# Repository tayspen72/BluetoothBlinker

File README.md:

Objective:
The goal of the project is to help myself become more familiar with the electronics design process. This includes:
* Schematic Design
* Component Selection
* PCB Layout
* Initial Board Bring-Up and Verification
* Firmware Development
* Evaluate Rust in an embedded microcontroller application

Plan
Build a PCB project with a similar purpose to a manufacturer evalutation kit with the following requirements:
* Bluetooth connectivity
* IO available with _reasonable_ function through peripherals
* Connectible to PC using USB-C
* Logging through UART when connected to PC

Conclusion:
The board design was completed and peer reviewed (by coworker)
Samples were ordered through PCB way and digikey for components
Samples were hand assembled (with blood sweat and tears)
Issue in the inline fuse, replaced with 0R resistor to advance in design
Board is functional, able to program and toggle LED using available IO
Bluetooth connectivity is pending..

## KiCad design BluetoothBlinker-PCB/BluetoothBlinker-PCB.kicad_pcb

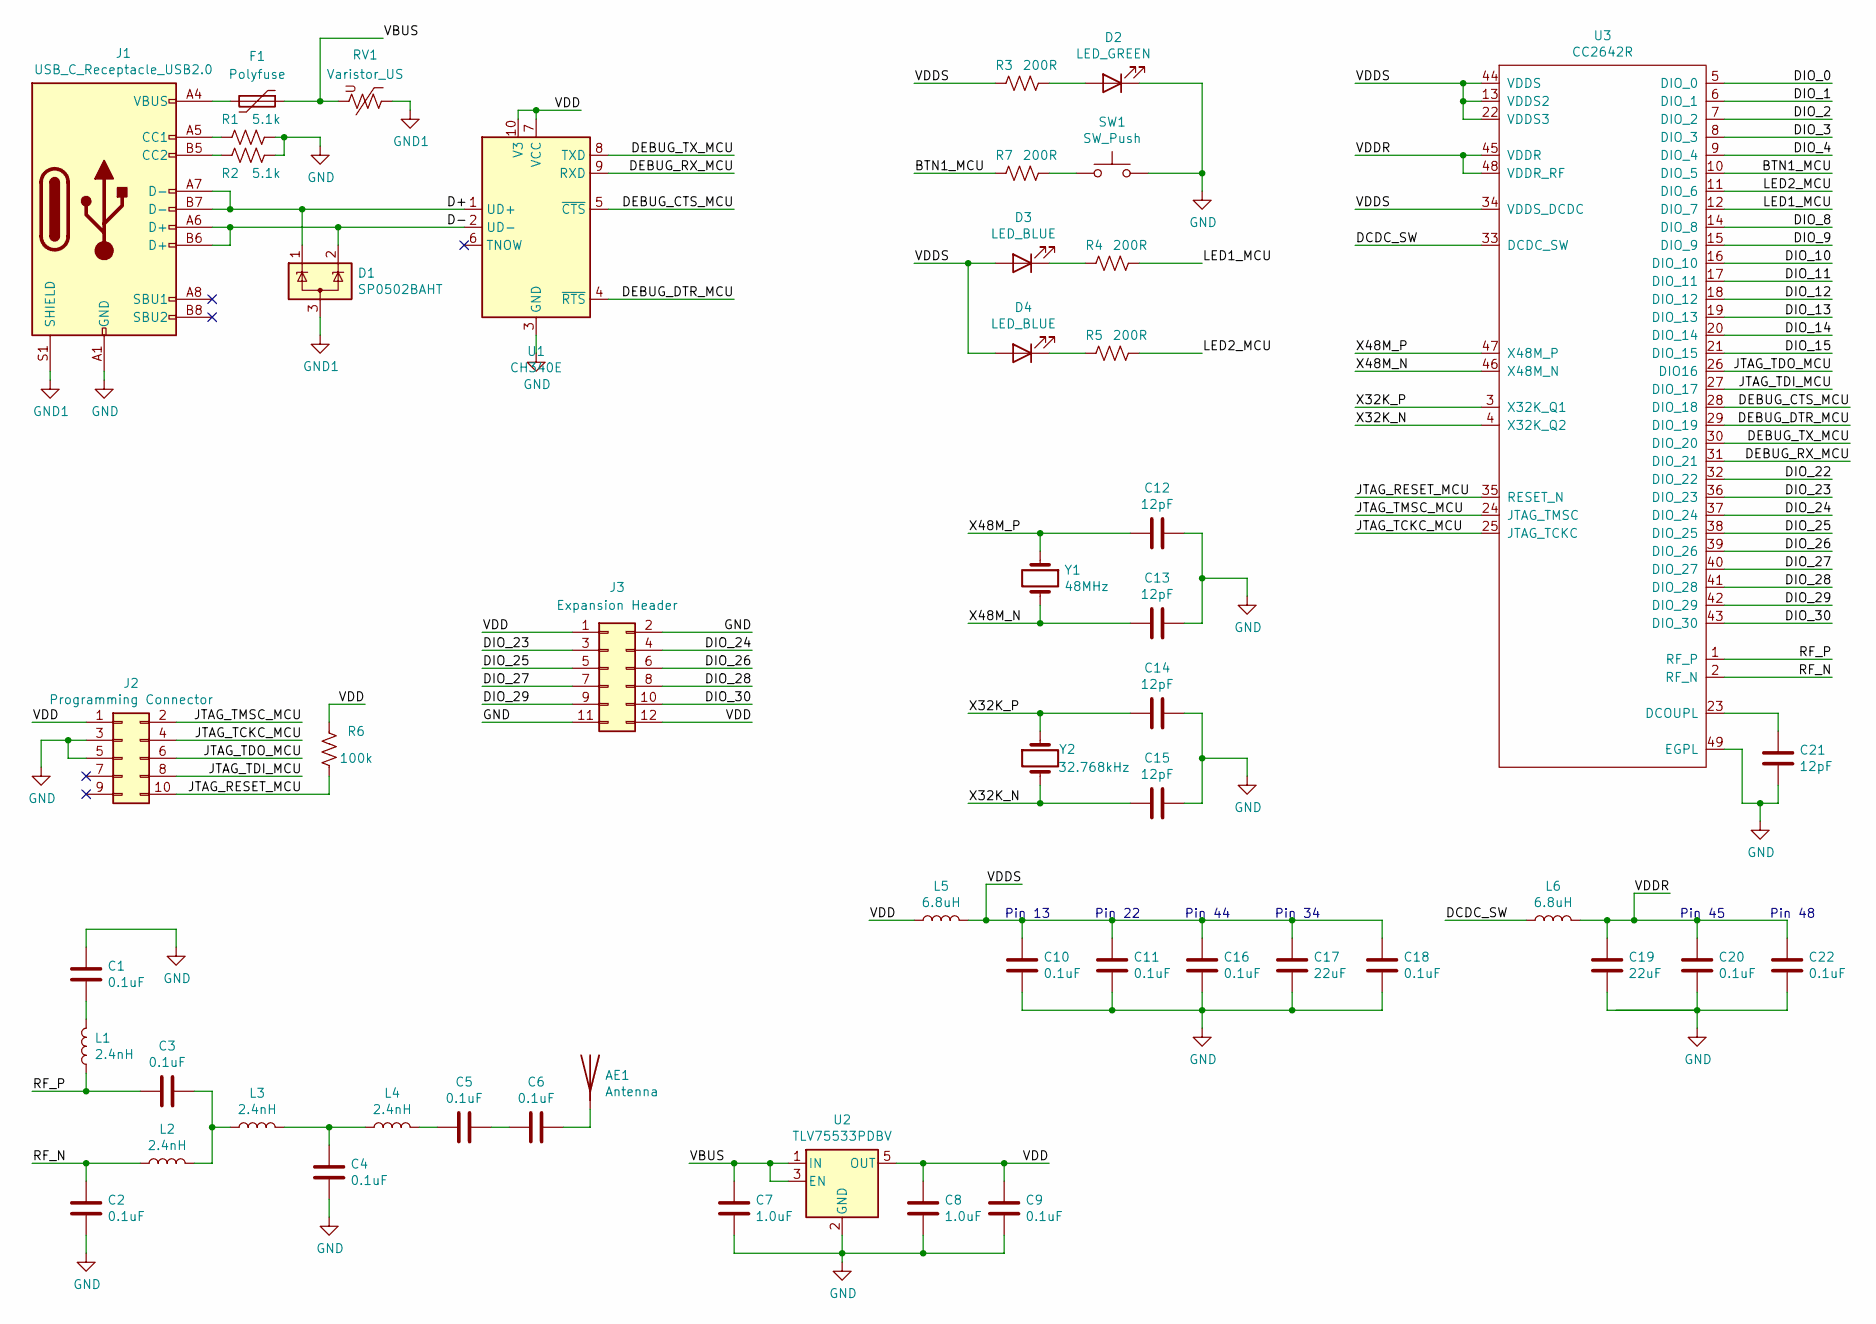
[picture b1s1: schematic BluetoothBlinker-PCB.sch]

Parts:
AE1: Antenna; Texas_SWRA117D_2.4GHz_Right
C1, C2, C3, C4, C5, C6, C9, C10, C11, C16, C18, C20, C22: 0.1uF; C_0603_1608Metric
C7, C8: 1.0uF; C_0603_1608Metric
C12, C13, C14, C15, C21: 12pF; C_0603_1608Metric
C17, C19: 22uF; C_0603_1608Metric
D1: SP0502BAHT; SOT-23
D2: LED_GREEN; LED_0603_1608Metric
D3, D4: LED_BLUE; LED_0603_1608Metric
F1: Polyfuse; R_1206_3216Metric
J1: USB_C_Receptacle_USB2.0; USB_C_Receptacle_GCT_USB4085
J2: Programming Connector; PinHeader_2x05_P1.27mm_Vertical
J3: Expansion Header; PinHeader_2x06_P2.54mm_Vertical
L1, L2, L3, L4: 2.4nH; L_0603_1608Metric
L5, L6: 6.8uH; L_0603_1608Metric
R1, R2: 5.1k; R_0603_1608Metric
R3, R4, R5, R7: 200R; R_0603_1608Metric
R6: 100k; R_0603_1608Metric
RV1: Varistor_US; R_0603_1608Metric
SW1: SW_Push; SW_PUSH_6mm
U1: CH340E; MSOP-10_3x3mm_P0.5mm
U2: TLV75533PDBV; SOT-23-5
U3: CC2642R
Y1: 48MHz; Crystal_HC49-U_Vertical
Y2: 32.768kHz; Crystal_C26-LF_D2.1mm_L6.5mm_Horizontal

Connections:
/BTN1_MCU: R7.1, U3.10 (DIO_5)
/D+: D1.1 (K), J1.A7 (D-), J1.B7 (D-), U1.1 (UD+)
/D-: D1.2 (K), J1.A6 (D+), J1.B6 (D+), U1.2 (UD-)
/DCDC_SW: L6.1, U3.33 (DCDC_SW)
/DEBUG_CTS_MCU: U1.5 (~CTS), U3.28 (DIO_18)
/DEBUG_DTR_MCU: U1.4 (~RTS), U3.29 (DIO_19)
/DEBUG_RX_MCU: U1.9 (RXD), U3.31 (DIO_21)
/DEBUG_TX_MCU: U1.8 (TXD), U3.30 (DIO_20)
/DIO_0: U3.5 (DIO_0)
/DIO_1: U3.6 (DIO_1)
/DIO_2: U3.7 (DIO_2)
/DIO_3: U3.8 (DIO_3)
/DIO_4: U3.9 (DIO_4)
/DIO_8: U3.14 (DIO_8)
/DIO_9: U3.15 (DIO_9)
/DIO_10: U3.16 (DIO_10)
/DIO_11: U3.17 (DIO_11)
/DIO_12: U3.18 (DIO_12)
/DIO_13: U3.19 (DIO_13)
/DIO_14: U3.20 (DIO_14)
/DIO_15: U3.21 (DIO_15)
/DIO_22: U3.32 (DIO_22)
/DIO_23: J3.3, U3.36 (DIO_23)
/DIO_24: J3.4, U3.37 (DIO_24)
/DIO_25: J3.5, U3.38 (DIO_25)
/DIO_26: J3.6, U3.39 (DIO_26)
/DIO_27: J3.7, U3.40 (DIO_27)
/DIO_28: J3.8, U3.41 (DIO_28)
/DIO_29: J3.9, U3.42 (DIO_29)
/DIO_30: J3.10, U3.43 (DIO_30)
/JTAG_RESET_MCU: J2.10, R6.1, U3.35 (RESET_N)
/JTAG_TCKC_MCU: J2.4, U3.25 (JTAG_TCKC)
/JTAG_TDI_MCU: J2.8, U3.27 (DIO_17)
/JTAG_TDO_MCU: J2.6, U3.26 (DIO16)
/JTAG_TMSC_MCU: J2.2, U3.24 (JTAG_TMSC)
/LED1_MCU: R4.2, U3.12 (DIO_7)
/LED2_MCU: R5.2, U3.11 (DIO_6)
/RF_N: C2.1, L2.1, U3.2 (RF_N)
/RF_P: C3.2, L1.1, U3.1 (RF_P)
/VBUS: C7.1, F1.1, RV1.2, U2.1 (IN), U2.3 (EN)
/VDD: C8.1, C9.1, J2.1, J3.1, J3.12, L5.1, R6.2, U1.7 (VCC), U1.10 (V3), U2.5 (OUT)
/VDDR: C19.1, C20.1, C22.1, L6.2, U3.45 (VDDR), U3.48 (VDDR_RF)
/VDDS: C10.1, C11.1, C16.1, C17.1, C18.1, D3.2 (A), D4.2 (A), L5.2, R3.1, U3.13 (VDDS2), U3.22 (VDDS3), U3.34 (VDDS_DCDC), U3.44 (VDDS)
/X32K_N: C15.2, U3.4 (X32K_Q2), Y2.2
/X32K_P: C14.2, U3.3 (X32K_Q1), Y2.1
/X48M_N: C13.2, U3.46 (X48M_N), Y1.2
/X48M_P: C12.2, U3.47 (X48M_P), Y1.1
GND: C1.2, C2.2, C4.2, C7.2, C8.2, C9.2, C10.2, C11.2, C12.1, C13.1, C14.1, C15.1, C16.2, C17.2, C18.2, C19.2, C20.2, C21.1, C22.2, D2.1 (K), J1.A1 (GND), J1.A12 (GND), J1.B1 (GND), J1.B12 (GND), J2.3, J2.5, J3.2, J3.11, R1.1, R2.1, SW1.2, U1.3 (GND), U2.2 (GND), U3.49 (EGPL)
GND1: D1.3 (A), J1.S1 (SHIELD), RV1.1
unnamed: AE1.1, C6.1
unnamed: C1.1, L1.2
unnamed: C3.1, L2.2, L3.1
unnamed: C4.1, L3.2, L4.1
unnamed: C5.1, C6.2
unnamed: C5.2, L4.2
unnamed: C21.2, U3.23 (DCOUPL)
unnamed: D2.2 (A), R3.2
unnamed: D3.1 (K), R4.1
unnamed: D4.1 (K), R5.1
unnamed: F1.2, J1.A4 (VBUS), J1.A9 (VBUS), J1.B4 (VBUS), J1.B9 (VBUS)
unnamed: J1.A5 (CC1), R1.2
unnamed: J1.B5 (CC2), R2.2
unnamed: R7.2, SW1.1

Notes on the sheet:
Pin 45
Pin 48
Pin 13
Pin 22
Pin 44
Pin 34

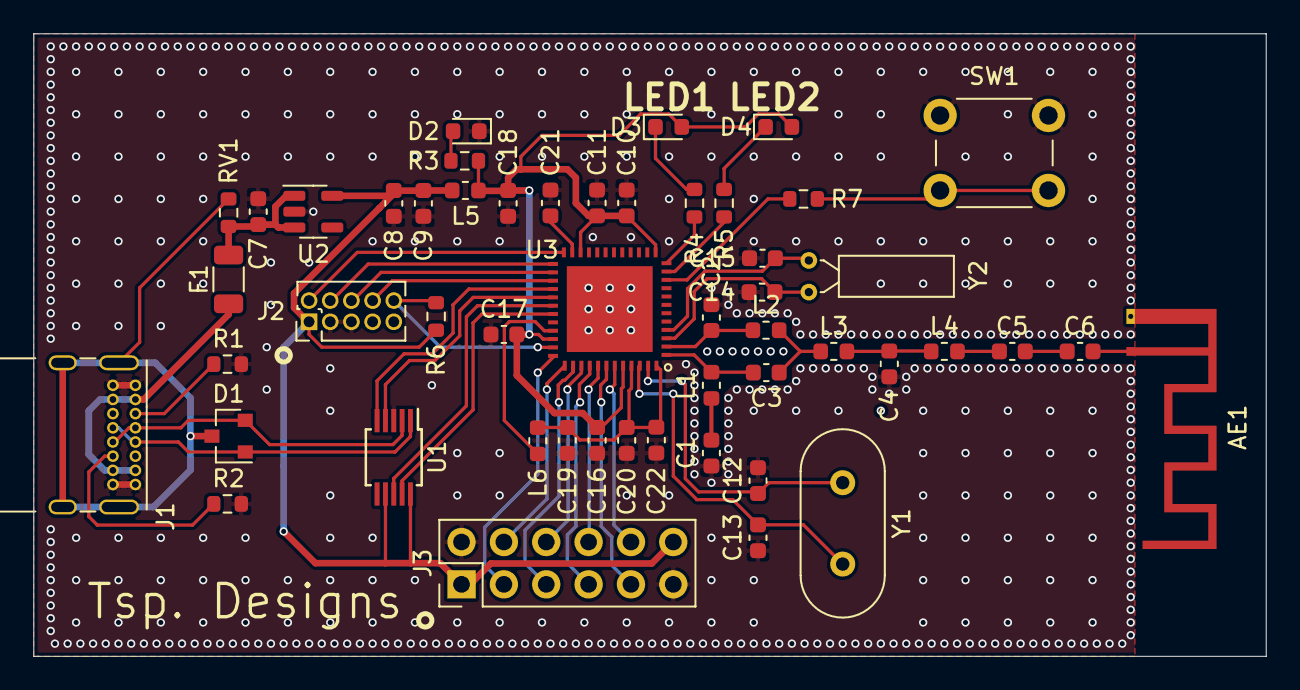
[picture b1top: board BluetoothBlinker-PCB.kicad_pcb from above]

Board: 2 copper layers, 73.9 x 37.3 mm, 51 parts (0 on the bottom side), 49 nets.

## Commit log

2021-04-05 Added BOM for v1.0
2021-05-05 Update to new USB Uart and generate PDF
2021-05-07 Initial commit of Rust project
2021-05-07 Initial bindings and config
2021-05-11 Adding in core peripherals
2021-05-12 Updated config and jlink server settings files
2021-05-12 Added script for starting the server
2021-05-12 Try this
2021-05-12 Try this for better debugging
2021-05-17 Update to use pac from github
2021-05-17 Added resources folder
2021-05-19 Update to use MCP432 launchpad as MCU
2021-05-19 Adding MCP432 resources
2021-05-24 begin testing
2021-08-16 Minor updates
2021-11-04 Allow for c and rust versions of app dev
2021-11-04 Adding c version of app
2021-11-04 Removed old rust files
2021-11-04 Adding makefile - not working
2021-11-04 Updating gitignore
2021-11-04 Functional makefile
2021-11-05 Fixed building issues, added debugger configs
2021-11-05 Working on linker
2021-11-08 Updates for functional compile
2021-11-08 Adding documentation
2021-11-08 Begin work on gpio config and control
